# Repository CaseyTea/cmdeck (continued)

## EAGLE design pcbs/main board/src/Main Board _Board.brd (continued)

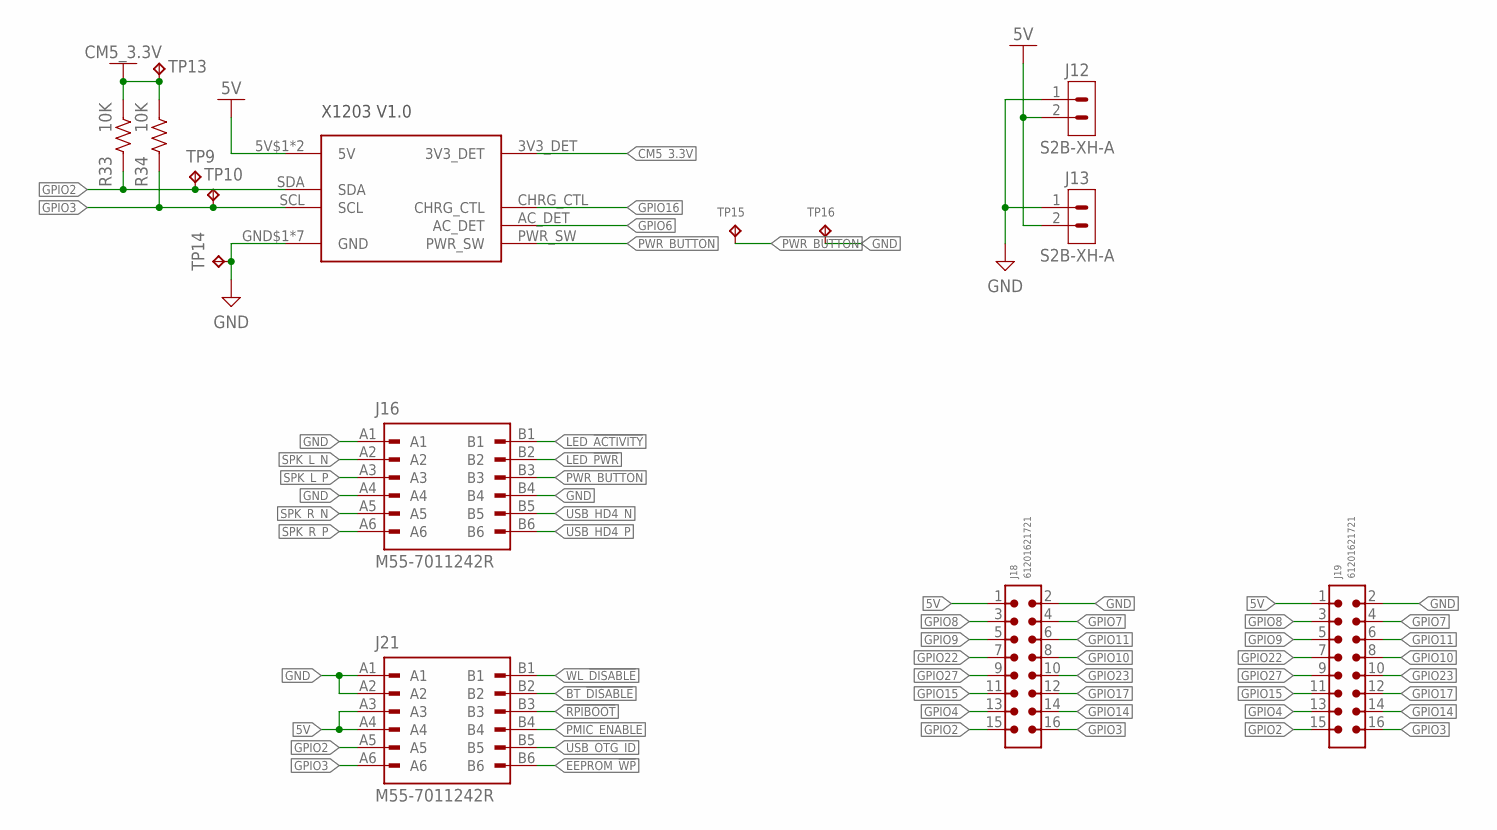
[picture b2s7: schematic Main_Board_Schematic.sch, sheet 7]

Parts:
J12, J13: S2B-XH-A
J16, J21: M55-7011242R; HARWIN_M55-7011242R
J18, J19: 61201621721
R33, R34: 10K; RESC2012X65
TP9, TP10, TP13, TP14: TPB1,27; B1,27
TP15, TP16: TPPAD1-13; P1-13
U$1: X1203

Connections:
5V: J12.2, J13.2, J18.1, J19.1, J21.A3, J21.A4, U$1.5V$1 (5V), U$1.5V$2 (5V); also elsewhere on the board
!RPIBOOT: J21.B3; also elsewhere on the board
BT_!DISABLE: J21.B2; also elsewhere on the board
CM5_3.3V: R33.2, R34.2, TP13.TP, U$1.3V3_DET; also elsewhere on the board
EEPROM_!WP: J21.B6; also elsewhere on the board
GND: J12.1, J13.1, J16.A1, J16.A4, J16.B4, J18.2, J19.2, J21.A1, J21.A2, TP14.TP, TP16.TP, U$1.GND$1 (GND), U$1.GND$2 (GND), U$1.GND$3 (GND), U$1.GND$4 (GND), U$1.GND$5 (GND), U$1.GND$6 (GND), U$1.GND$7 (GND); also elsewhere on the board
GPIO2: J18.15, J19.15, J21.A5, R33.1, TP9.TP, U$1.SDA; also elsewhere on the board
GPIO3: J18.16, J19.16, J21.A6, R34.1, TP10.TP, U$1.SCL; also elsewhere on the board
GPIO4: J18.13, J19.13; also elsewhere on the board
GPIO6: U$1.AC_DET; also elsewhere on the board
GPIO7: J18.4, J19.4; also elsewhere on the board
GPIO8: J18.3, J19.3; also elsewhere on the board
GPIO9: J18.5, J19.5; also elsewhere on the board
GPIO10: J18.8, J19.8; also elsewhere on the board
GPIO11: J18.6, J19.6; also elsewhere on the board
GPIO14: J18.14, J19.14; also elsewhere on the board
GPIO15: J18.11, J19.11; also elsewhere on the board
GPIO16: U$1.CHRG_CTL; also elsewhere on the board
GPIO17: J18.12, J19.12; also elsewhere on the board
GPIO22: J18.7, J19.7; also elsewhere on the board
GPIO23: J18.10, J19.10; also elsewhere on the board
GPIO27: J18.9, J19.9; also elsewhere on the board
LED_!ACTIVITY: J16.B1; also elsewhere on the board
LED_!PWR: J16.B2; also elsewhere on the board
PMIC_ENABLE: J21.B4; also elsewhere on the board
PWR_BUTTON: J16.B3, TP15.TP, U$1.PWR_SW; also elsewhere on the board
SPK_L_N: J16.A2; also elsewhere on the board
SPK_L_P: J16.A3; also elsewhere on the board
SPK_R_N: J16.A5; also elsewhere on the board
SPK_R_P: J16.A6; also elsewhere on the board
USB_HD4_N: J16.B5; also elsewhere on the board
USB_HD4_P: J16.B6; also elsewhere on the board
USB_OTG_ID: J21.B5; also elsewhere on the board
WL_!DISABLE: J21.B1; also elsewhere on the board

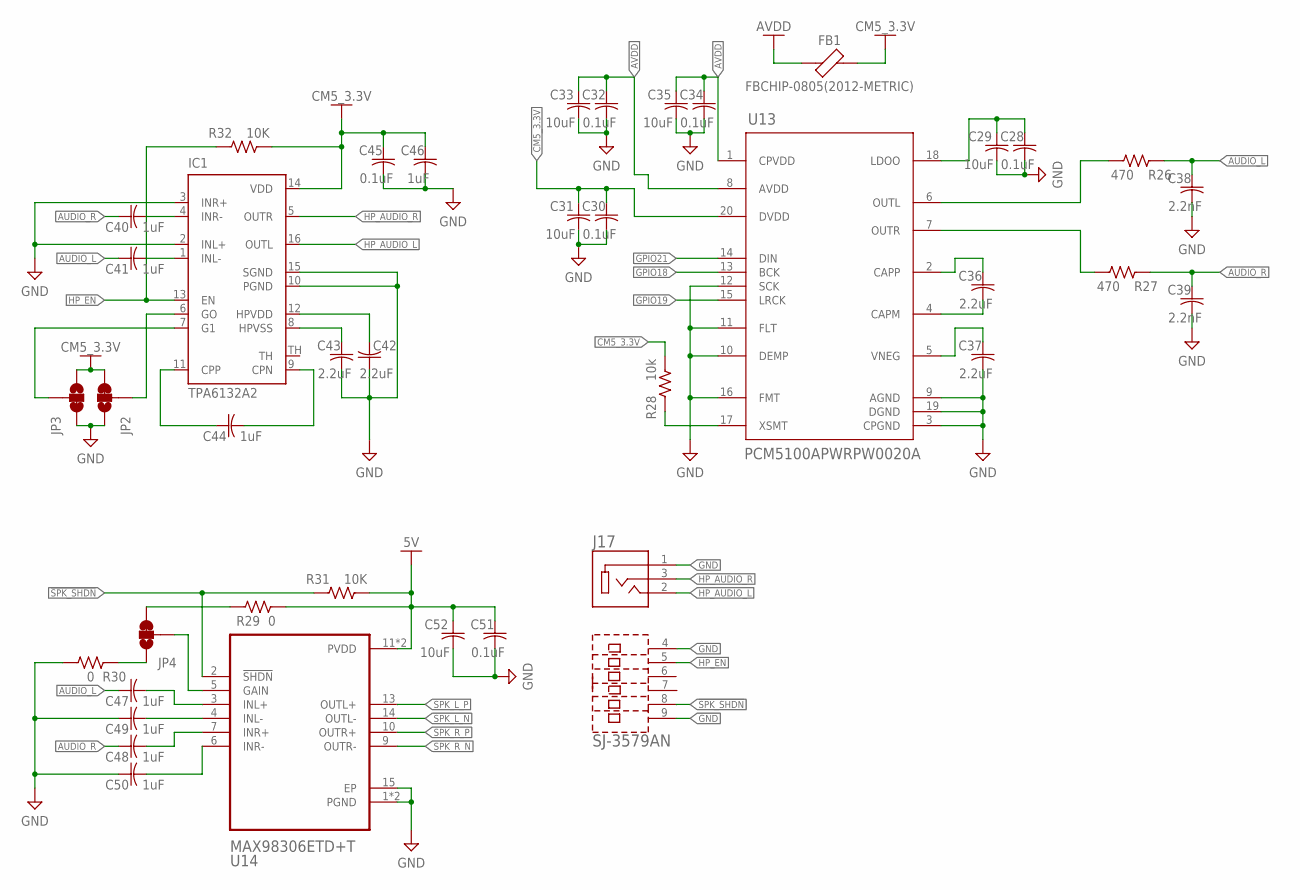
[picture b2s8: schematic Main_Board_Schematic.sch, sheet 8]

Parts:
C28, C30, C32, C34, C45, C51: 0.1uF; CAPC2012X110
C29, C31, C33, C35, C52: 10uF; CAPC3216X135
C36, C37, C42, C43: 2.2uF; CAPC2012X110
C38, C39: 2.2nF; CAPC2012X110
C40, C41, C44, C46, C47, C48, C49, C50: 1uF; CAPC2012X110
FB1: FBCHIP-0805(2012-METRIC); BEADC2012X105N
IC1: TPA6132A2; QFN16
J17: SJ-3579AN; CUI_SJ-3579AN
JP2, JP3, JP4: JUMPER-SMT_3_1-NC_TRACE_SILK; SMT-JUMPER_3_1-NC_TRACE_SILK
R26, R27: 470; RESC2012X65
R28: 10k; RESC2012X65
R29, R30: 0; RESC2012X65
R31, R32: 10K; RESC2012X65
U13: PCM5100APWRPW0020A; PW0020A
U14: MAX98306ETD+T; SON40P300X300X80-15N

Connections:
5V: C51.1, C52.1, R29.2, R31.2, U14.11 (PVDD), U14.12 (PVDD); also elsewhere on the board
!SPK_SHDN: J17.8, R31.1, U14.2 (!SHDN)
AUDIO_L: C38.1, C41.1, C47.1, R26.1
AUDIO_R: C39.1, C40.1, C48.1, R27.1
AVDD: C32.1, C33.1, C34.1, C35.1, FB1.1, U13.1 (CPVDD), U13.8 (AVDD)
CM5_3.3V: C30.1, C31.1, C45.1, C46.1, FB1.2, IC1.14 (VDD), JP2.3, JP3.1, R28.2, R32.2, U13.20 (DVDD); also elsewhere on the board
GND: C28.2, C29.2, C30.2, C31.2, C32.2, C33.2, C34.2, C35.2, C37.2, C38.2, C39.2, C42.1, C43.2, C45.2, C46.2, C49.1, C50.1, C51.2, C52.2, IC1.2 (INL+), IC1.3 (INR+), IC1.10 (PGND), IC1.15 (SGND), J17.1, J17.4, J17.9, JP2.1, JP3.3, R30.2, U13.3 (CPGND), U13.9 (AGND), U13.10 (DEMP), U13.11 (FLT), U13.12 (SCK), U13.16 (FMT), U13.19 (DGND), U14.1 (PGND), U14.8 (PGND), U14.15 (EP); also elsewhere on the board
GPIO18: U13.13 (BCK); also elsewhere on the board
GPIO19: U13.15 (LRCK); also elsewhere on the board
GPIO21: U13.14 (DIN); also elsewhere on the board
HP_AUDIO_L: IC1.16 (OUTL), J17.2
HP_AUDIO_R: IC1.5 (OUTR), J17.3
HP_EN: IC1.13 (EN), J17.5, R32.1
HP_G0: IC1.6 (GO), JP2.2
HP_G1: IC1.7 (G1), JP3.2
unnamed: R26.2, U13.6 (OUTL)
unnamed: R27.2, U13.7 (OUTR)
unnamed: C28.1, C29.1, U13.18 (LDOO)
unnamed: C36.1, U13.2 (CAPP)
unnamed: C36.2, U13.4 (CAPM)
unnamed: C37.1, U13.5 (VNEG)
unnamed: R28.1, U13.17 (XSMT)
unnamed: C41.2, IC1.1 (INL-)
unnamed: C40.2, IC1.4 (INR-)
unnamed: C43.1, IC1.8 (HPVSS)
unnamed: C42.2, IC1.12 (HPVDD)
unnamed: C44.2, IC1.9 (CPN)
unnamed: C44.1, IC1.11 (CPP)
unnamed: C49.2, U14.4 (INL-)
unnamed: C48.2, U14.7 (INR+)
unnamed: C47.2, U14.3 (INL+)
unnamed: C50.2, U14.6 (INR-)
unnamed: JP4.2, U14.5 (GAIN)
unnamed: JP4.1, R30.1
unnamed: JP4.3, R29.1
SPK_L_N: U14.14 (OUTL-); also elsewhere on the board
SPK_L_P: U14.13 (OUTL+); also elsewhere on the board
SPK_R_N: U14.9 (OUTR-); also elsewhere on the board
SPK_R_P: U14.10 (OUTR+); also elsewhere on the board

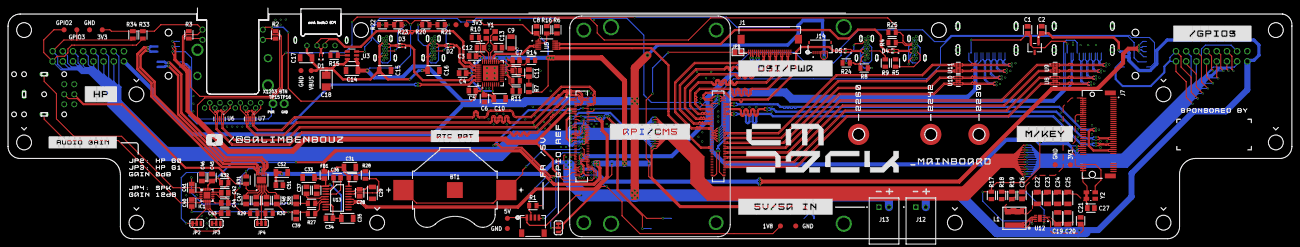
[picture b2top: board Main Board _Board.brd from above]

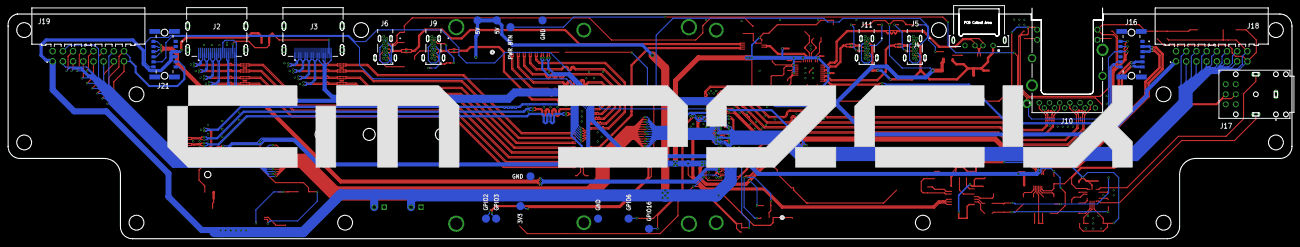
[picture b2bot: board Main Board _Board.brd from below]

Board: 4 copper layers, 320.0 x 57.5 mm, 152 parts (13 on the bottom side), 173 nets.

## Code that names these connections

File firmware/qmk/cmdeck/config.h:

#pragma once

/* OLED */
#define OLED_DISPLAY_128X64
#define OLED_IC OLED_IC_SH1106
#define OLED_DC_PIN GP23
#define OLED_CS_PIN GP22
#define OLED_RST_PIN GP24
#define OLED_SPI_DIVISOR 4
#define OLED_COLUMN_OFFSET 2

/* ChibiOS SPI definitions */
#define SPI_DRIVER SPID1
#define SPI_SCK_PIN GP26
#define SPI_MOSI_PIN GP27
#define SPI_MISO_PIN GP28

/* RGB MATRIX */
#define RGB_MATRIX_MAXIMUM_BRIGHTNESS 180
#define RGB_MATRIX_TIMEOUT 30000
#define RGB_MATRIX_SLEEP

/* MAGIC BOOT */
#define BOOTMAGIC_ROW 0
#define BOOTMAGIC_COLUMN 11

/* CIRQUE TRACKPAD*/
#define CIRQUE_PINNACLE_SPI_CS_PIN 25
#define CIRQUE_PINNACLE_TAP_ENABLE
#define POINTING_DEVICE_ROTATION_270
#define CIRQUE_PINNACLE_CURVED_OVERLAY
#define CIRQUE_PINNACLE_SECONDARY_TAP_ENABLE
#define CIRQUE_PINNACLE_ATTENUATION EXTREG__TRACK_ADCCONFIG__ADC_ATTENUATE_2X

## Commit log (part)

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2026-02-10 Video Upload
2026-02-10 Fix formatting in QMK readme
